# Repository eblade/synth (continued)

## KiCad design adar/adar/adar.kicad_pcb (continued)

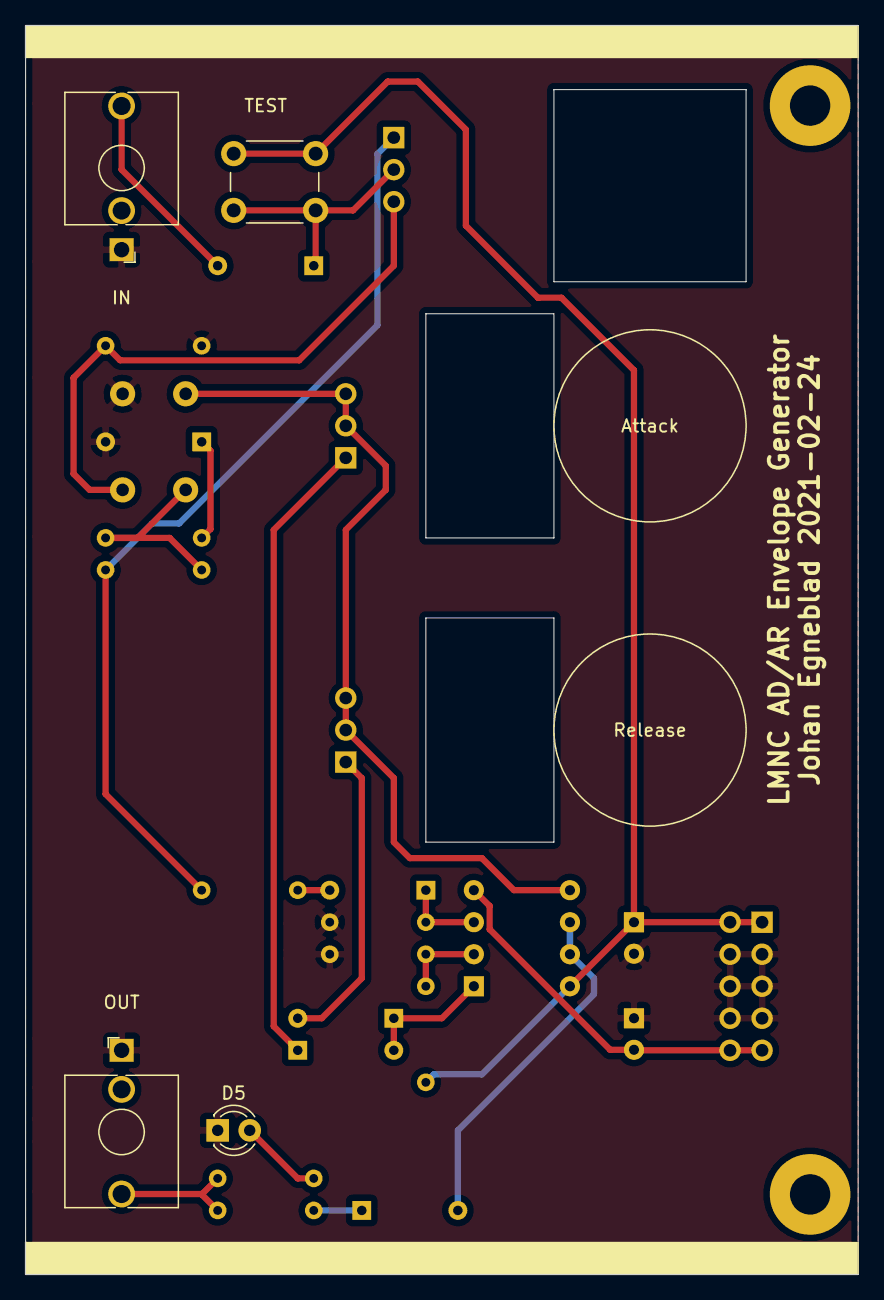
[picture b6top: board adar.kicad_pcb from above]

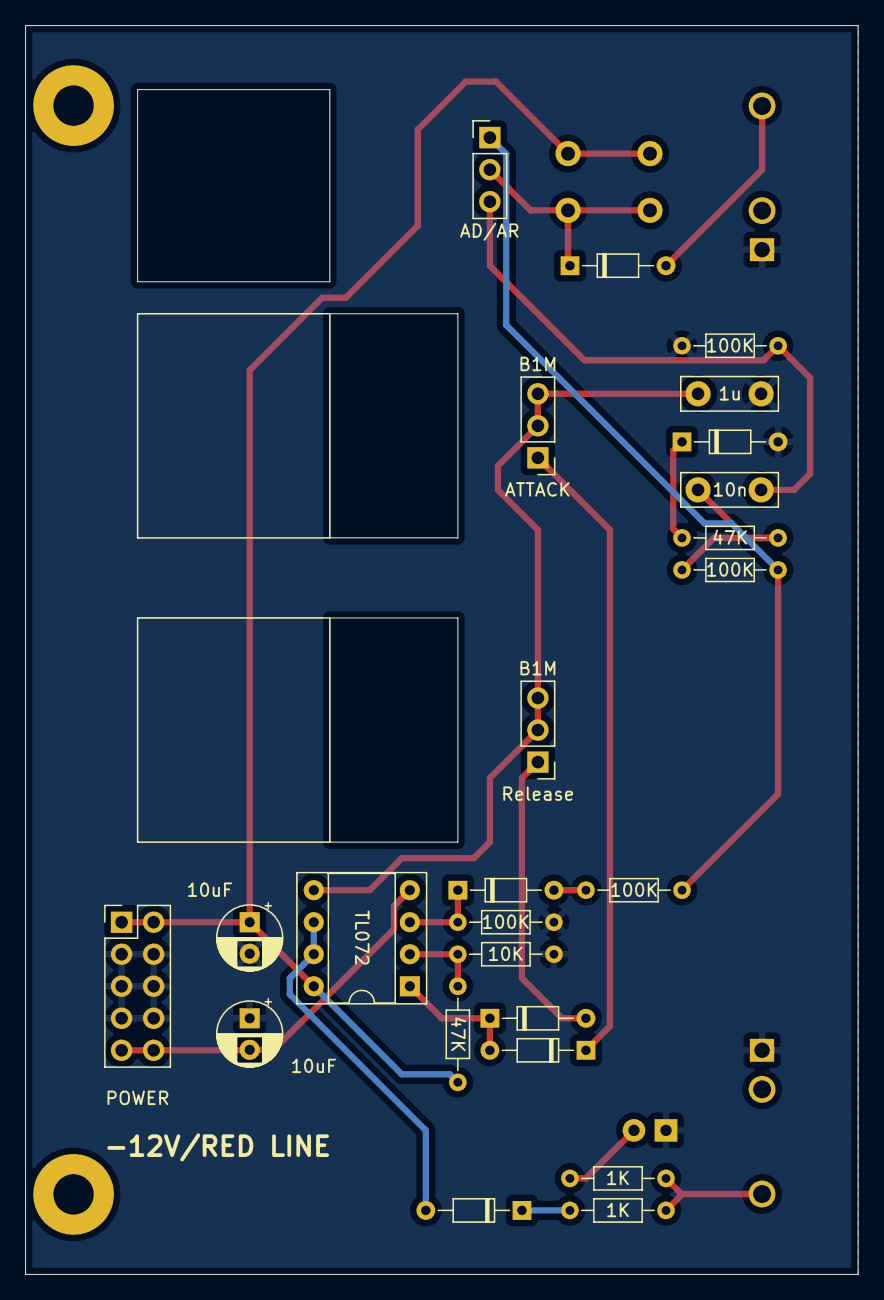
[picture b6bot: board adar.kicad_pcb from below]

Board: 2 copper layers, 66.0 x 99.1 mm, 30 parts (24 on the bottom side), 20 nets.

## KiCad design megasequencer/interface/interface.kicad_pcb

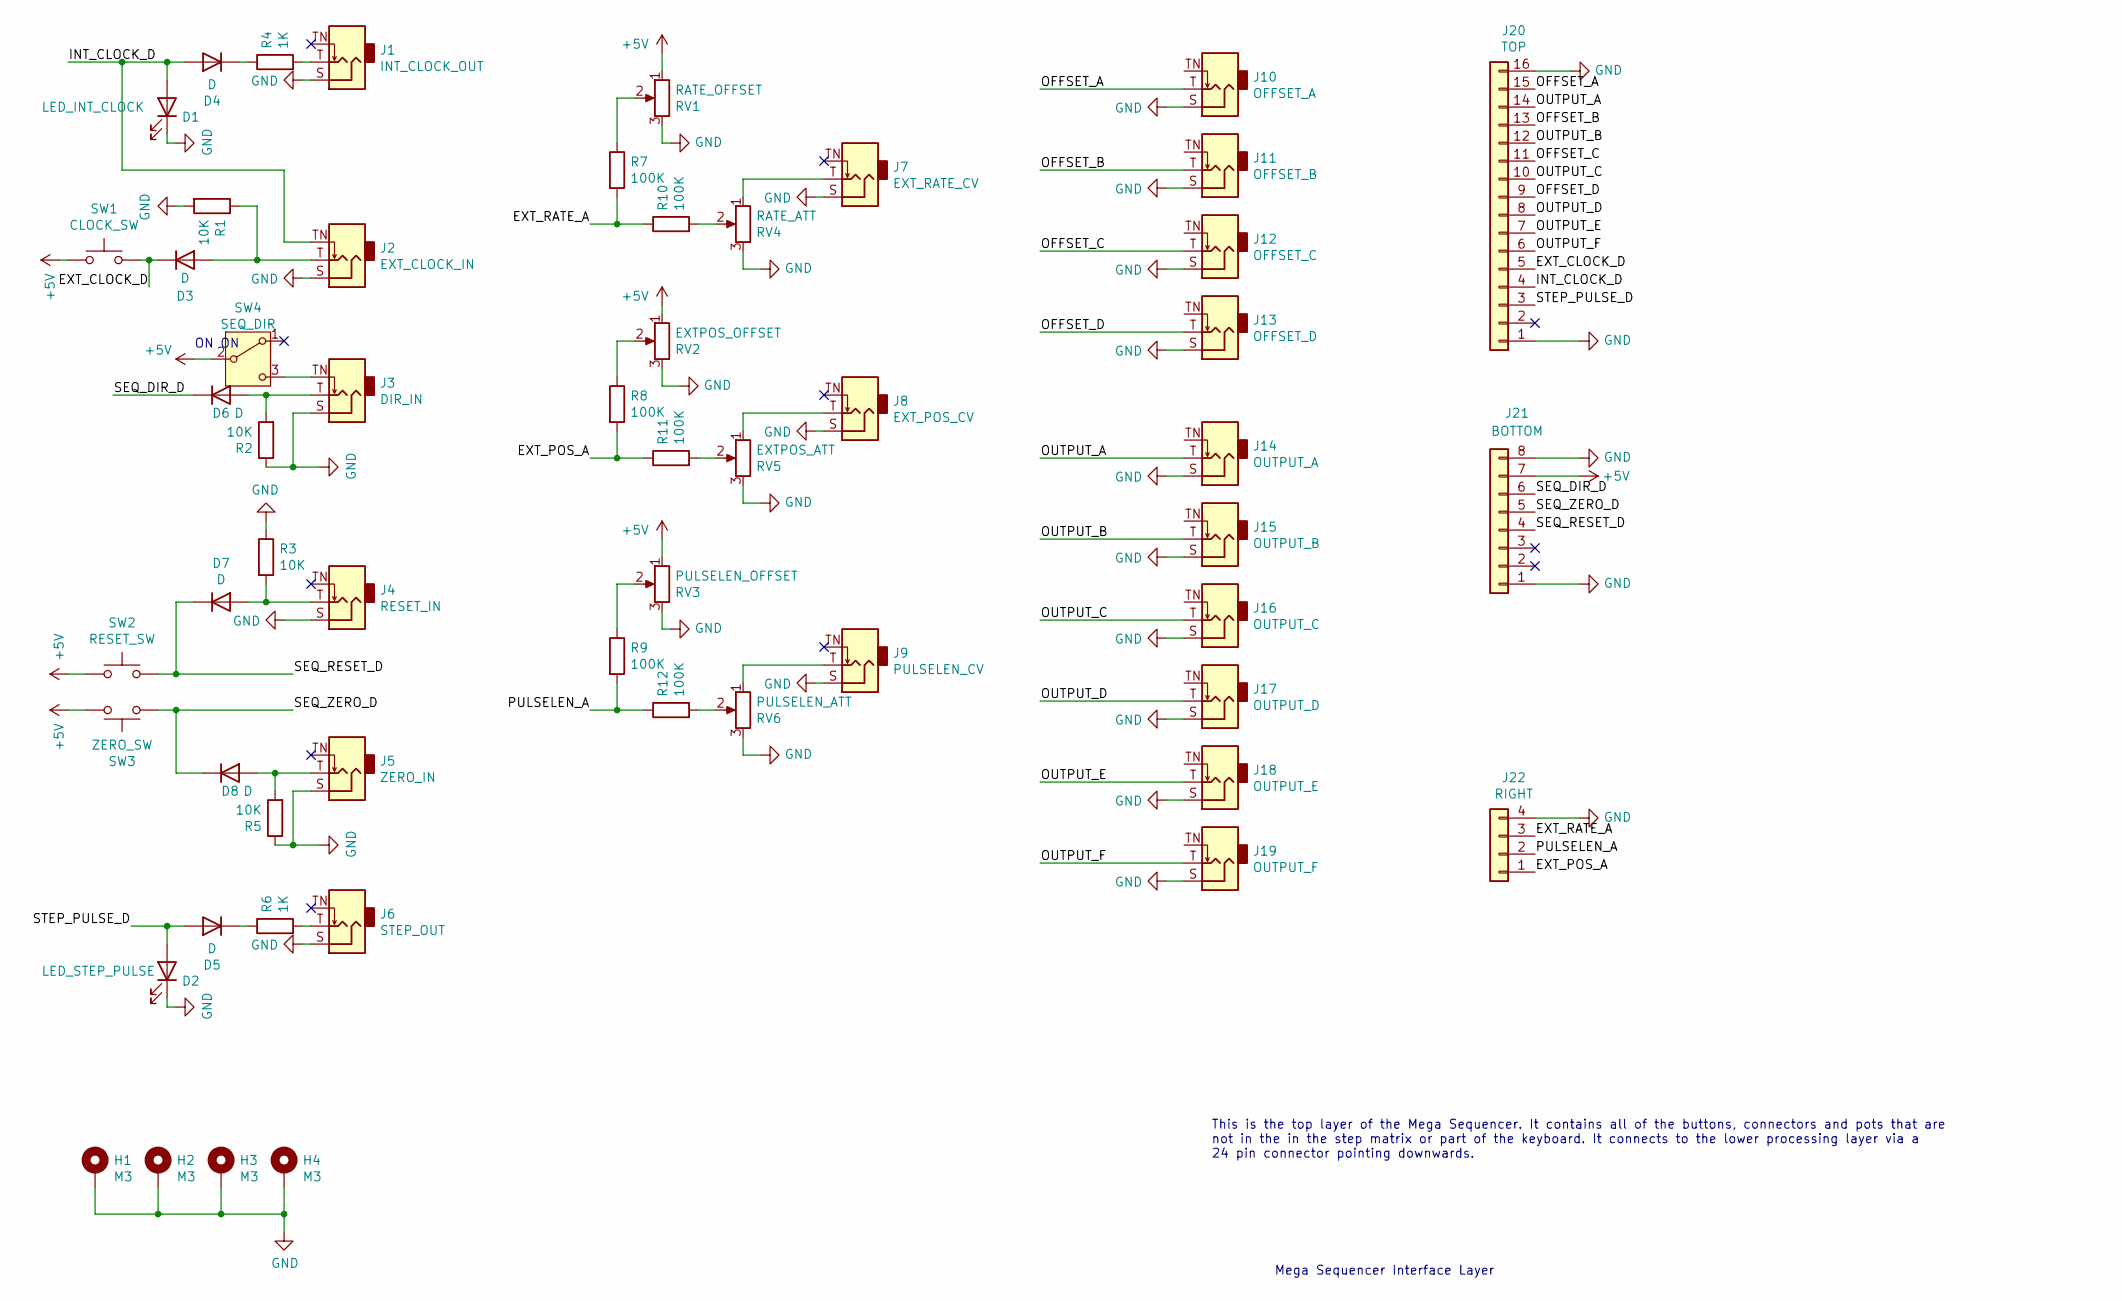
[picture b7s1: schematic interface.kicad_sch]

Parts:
D1: LED_INT_CLOCK; LED_D3.0mm
D2: LED_STEP_PULSE; LED_D3.0mm
D3, D4, D5, D6, D7, D8: D; D_DO-41_SOD81_P7.62mm_Horizontal
H1, H2, H3, H4: M3; MountingHole_3.2mm_M3_Pad
J1: INT_CLOCK_OUT; Jack_3.5mm_QingPu_WQP-PJ398SM_Vertical_CircularHoles
J2: EXT_CLOCK_IN; Jack_3.5mm_QingPu_WQP-PJ398SM_Vertical_CircularHoles
J3: DIR_IN; Jack_3.5mm_QingPu_WQP-PJ398SM_Vertical_CircularHoles
J4: RESET_IN; Jack_3.5mm_QingPu_WQP-PJ398SM_Vertical_CircularHoles
J5: ZERO_IN; Jack_3.5mm_QingPu_WQP-PJ398SM_Vertical_CircularHoles
J6: STEP_OUT; Jack_3.5mm_QingPu_WQP-PJ398SM_Vertical_CircularHoles
J7: EXT_RATE_CV; Jack_3.5mm_QingPu_WQP-PJ398SM_Vertical_CircularHoles
J8: EXT_POS_CV; Jack_3.5mm_QingPu_WQP-PJ398SM_Vertical_CircularHoles
J9: PULSELEN_CV; Jack_3.5mm_QingPu_WQP-PJ398SM_Vertical_CircularHoles
J10: OFFSET_A; Jack_3.5mm_QingPu_WQP-PJ398SM_Vertical_CircularHoles
J11: OFFSET_B; Jack_3.5mm_QingPu_WQP-PJ398SM_Vertical_CircularHoles
J12: OFFSET_C; Jack_3.5mm_QingPu_WQP-PJ398SM_Vertical_CircularHoles
J13: OFFSET_D; Jack_3.5mm_QingPu_WQP-PJ398SM_Vertical_CircularHoles
J14: OUTPUT_A; Jack_3.5mm_QingPu_WQP-PJ398SM_Vertical_CircularHoles
J15: OUTPUT_B; Jack_3.5mm_QingPu_WQP-PJ398SM_Vertical_CircularHoles
J16: OUTPUT_C; Jack_3.5mm_QingPu_WQP-PJ398SM_Vertical_CircularHoles
J17: OUTPUT_D; Jack_3.5mm_QingPu_WQP-PJ398SM_Vertical_CircularHoles
J18: OUTPUT_E; Jack_3.5mm_QingPu_WQP-PJ398SM_Vertical_CircularHoles
J19: OUTPUT_F; Jack_3.5mm_QingPu_WQP-PJ398SM_Vertical_CircularHoles
J20: TOP; PinHeader_1x16_P2.54mm_Vertical
J21: BOTTOM; PinHeader_1x08_P2.54mm_Vertical
J22: RIGHT; PinHeader_1x04_P2.54mm_Vertical
R1, R2, R3, R5: 10K; R_Axial_DIN0207_L6.3mm_D2.5mm_P7.62mm_Horizontal
R4, R6: 1K; R_Axial_DIN0207_L6.3mm_D2.5mm_P7.62mm_Horizontal
R7, R8, R9, R10, R11, R12: 100K; R_Axial_DIN0207_L6.3mm_D2.5mm_P7.62mm_Horizontal
RV1: RATE_OFFSET; Potentiometer_Alps_RK09L_Single_Vertical
RV2: EXTPOS_OFFSET; Potentiometer_Alps_RK09L_Single_Vertical
RV3: PULSELEN_OFFSET; Potentiometer_Alps_RK09L_Single_Vertical
RV4: RATE_ATT; Potentiometer_Alps_RK09L_Single_Vertical
RV5: EXTPOS_ATT; Potentiometer_Alps_RK09L_Single_Vertical
RV6: PULSELEN_ATT; Potentiometer_Alps_RK09L_Single_Vertical
SW1: CLOCK_SW; SW_PUSH_6mm
SW2: RESET_SW; SW_PUSH_6mm
SW3: ZERO_SW; SW_PUSH_6mm
SW4: SEQ_DIR; PinSocket_1x03_P2.54mm_Vertical

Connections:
+5V: J21.7, RV1.1, RV2.1, RV3.1, SW1.1, SW2.1, SW3.2, SW4.2 (B)
/EXT_CLOCK_D: D3.1 (K), J20.5, SW1.2
/EXT_POS_A: J22.1, R8.2, R11.1
/EXT_RATE_A: J22.3, R7.2, R10.1
/INT_CLOCK_D: D1.2 (A), D4.2 (A), J2.TN, J20.4
/OFFSET_A: J10.T, J20.15
/OFFSET_B: J11.T, J20.13
/OFFSET_C: J12.T, J20.11
/OFFSET_D: J13.T, J20.9
/OUTPUT_A: J14.T, J20.14
/OUTPUT_B: J15.T, J20.12
/OUTPUT_C: J16.T, J20.10
/OUTPUT_D: J17.T, J20.8
/OUTPUT_E: J18.T, J20.7
/OUTPUT_F: J19.T, J20.6
/PULSELEN_A: J22.2, R9.2, R12.1
/SEQ_DIR_D: D6.1 (K), J21.6
/SEQ_RESET_D: D7.1 (K), J21.4, SW2.2
/SEQ_ZERO_D: D8.1 (K), J21.5, SW3.1
/STEP_PULSE_D: D2.2 (A), D5.2 (A), J20.3
GND: D1.1 (K), D2.1 (K), H1.1, H2.1, H3.1, H4.1, J1.S, J2.S, J3.S, J4.S, J5.S, J6.S, J7.S, J8.S, J9.S, J10.S, J11.S, J12.S, J13.S, J14.S, J15.S, J16.S, J17.S, J18.S, J19.S, J20.1, J20.16, J21.1, J21.8, J22.4, R1.2, R2.1, R3.1, R5.1, RV1.3, RV2.3, RV3.3, RV4.3, RV5.3, RV6.3
unnamed: D3.2 (A), J2.T, R1.1
unnamed: D4.1 (K), R4.1
unnamed: D5.1 (K), R6.1
unnamed: D6.2 (A), J3.T, R2.2
unnamed: D7.2 (A), J4.T, R3.2
unnamed: D8.2 (A), J5.T, R5.2
unnamed: J1.T, R4.2
unnamed: J3.TN, SW4.3 (C)
unnamed: J6.T, R6.2
unnamed: J7.T, RV4.1
unnamed: J8.T, RV5.1
unnamed: J9.T, RV6.1
unnamed: R7.1, RV1.2
unnamed: R8.1, RV2.2
unnamed: R9.1, RV3.2
unnamed: R10.2, RV4.2
unnamed: R11.2, RV5.2
unnamed: R12.2, RV6.2

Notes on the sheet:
ON ON
Mega Sequencer Interface Layer
This is the top layer of the Mega Sequencer. It contains all of the buttons, connectors and pots that are not in the in the step matrix or part of the keyboard. It connects to the lower processing layer via a 24 pin connector pointing downwards.

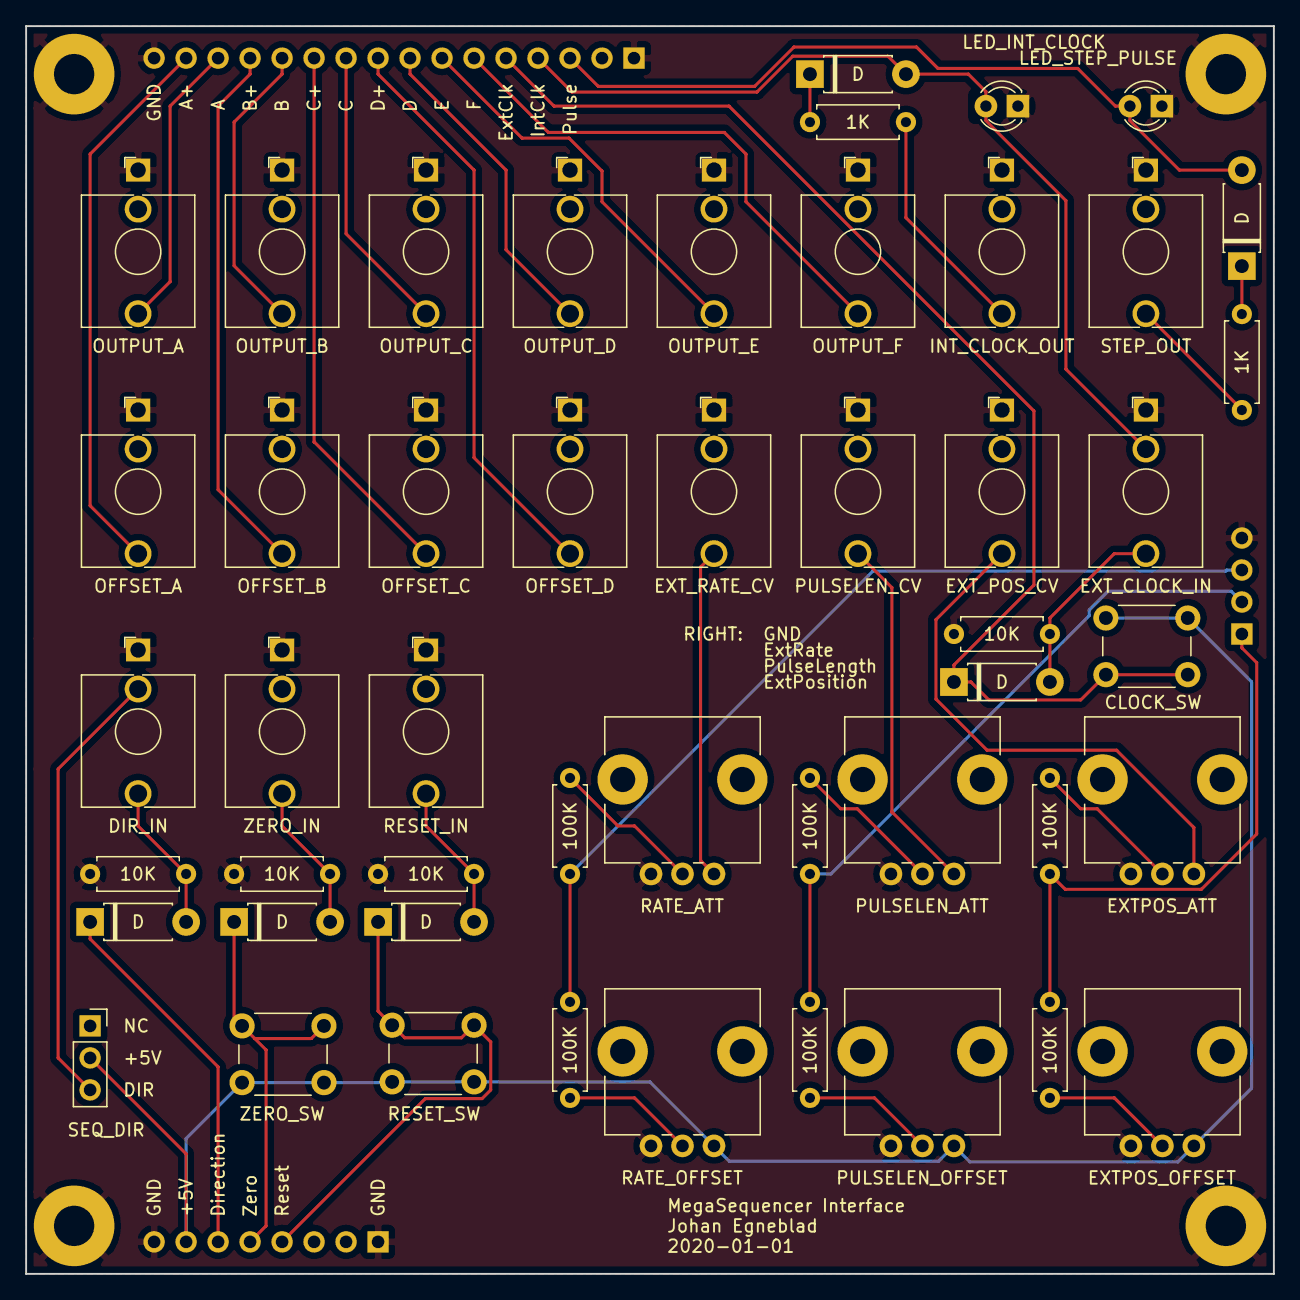
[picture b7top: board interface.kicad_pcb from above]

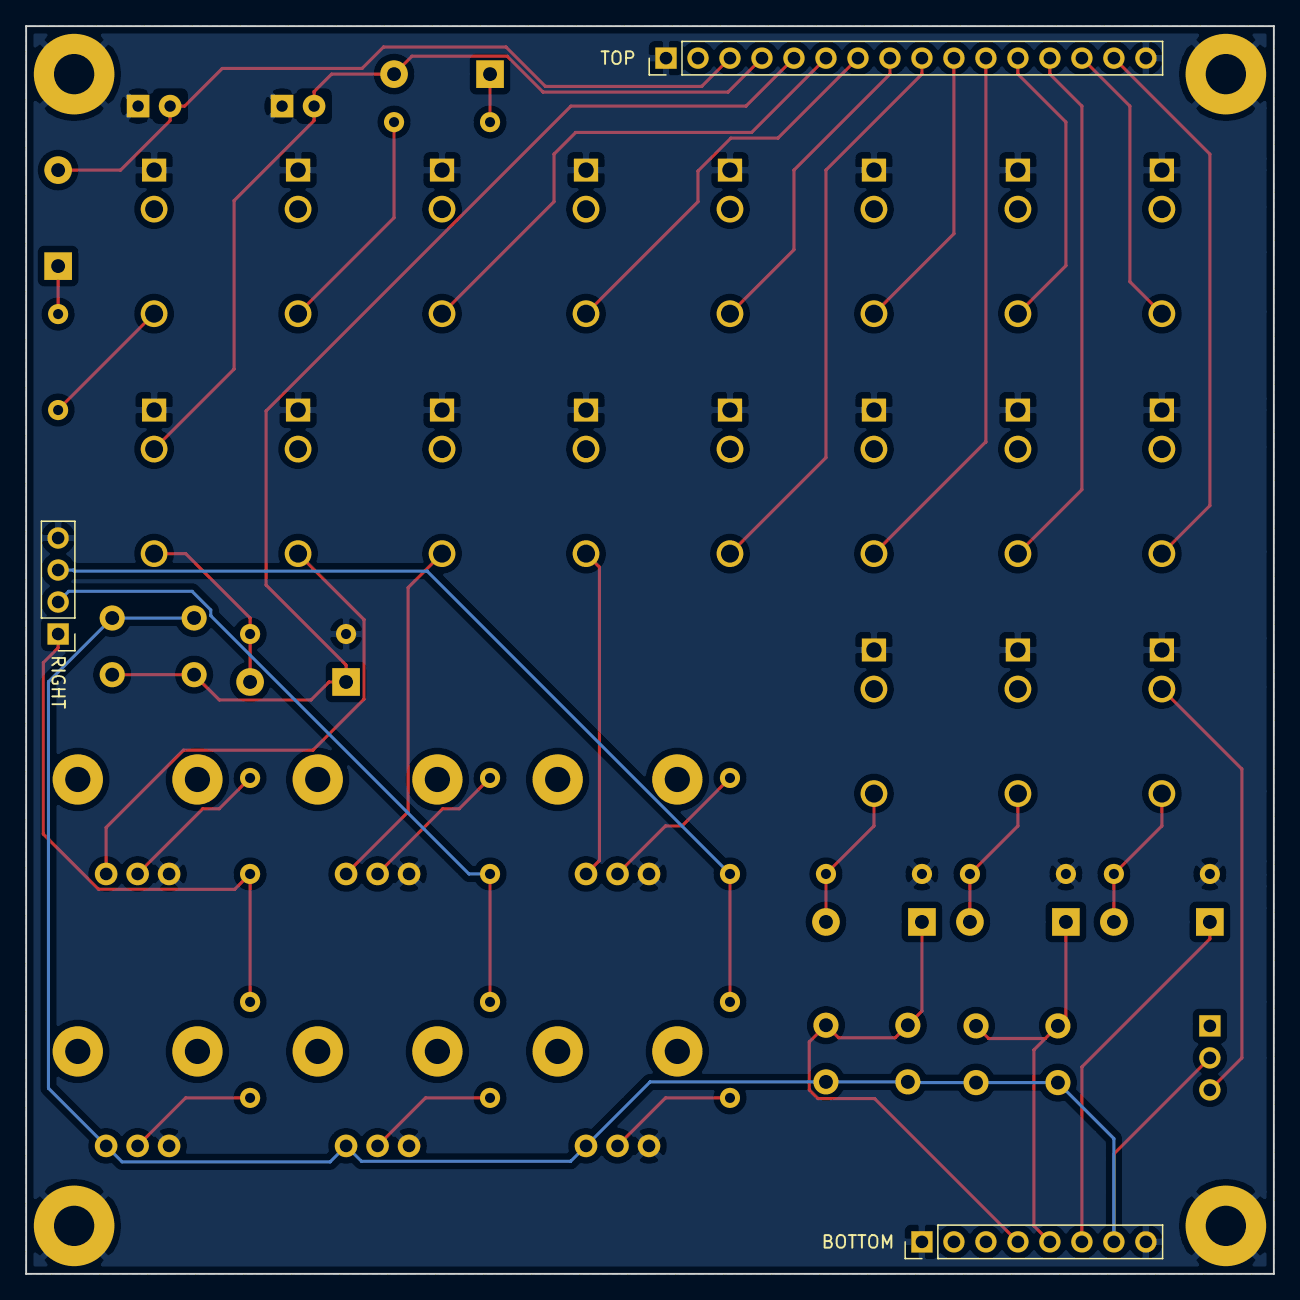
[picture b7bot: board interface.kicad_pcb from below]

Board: 2 copper layers, 99.1 x 99.1 mm, 56 parts (3 on the bottom side), 39 nets.

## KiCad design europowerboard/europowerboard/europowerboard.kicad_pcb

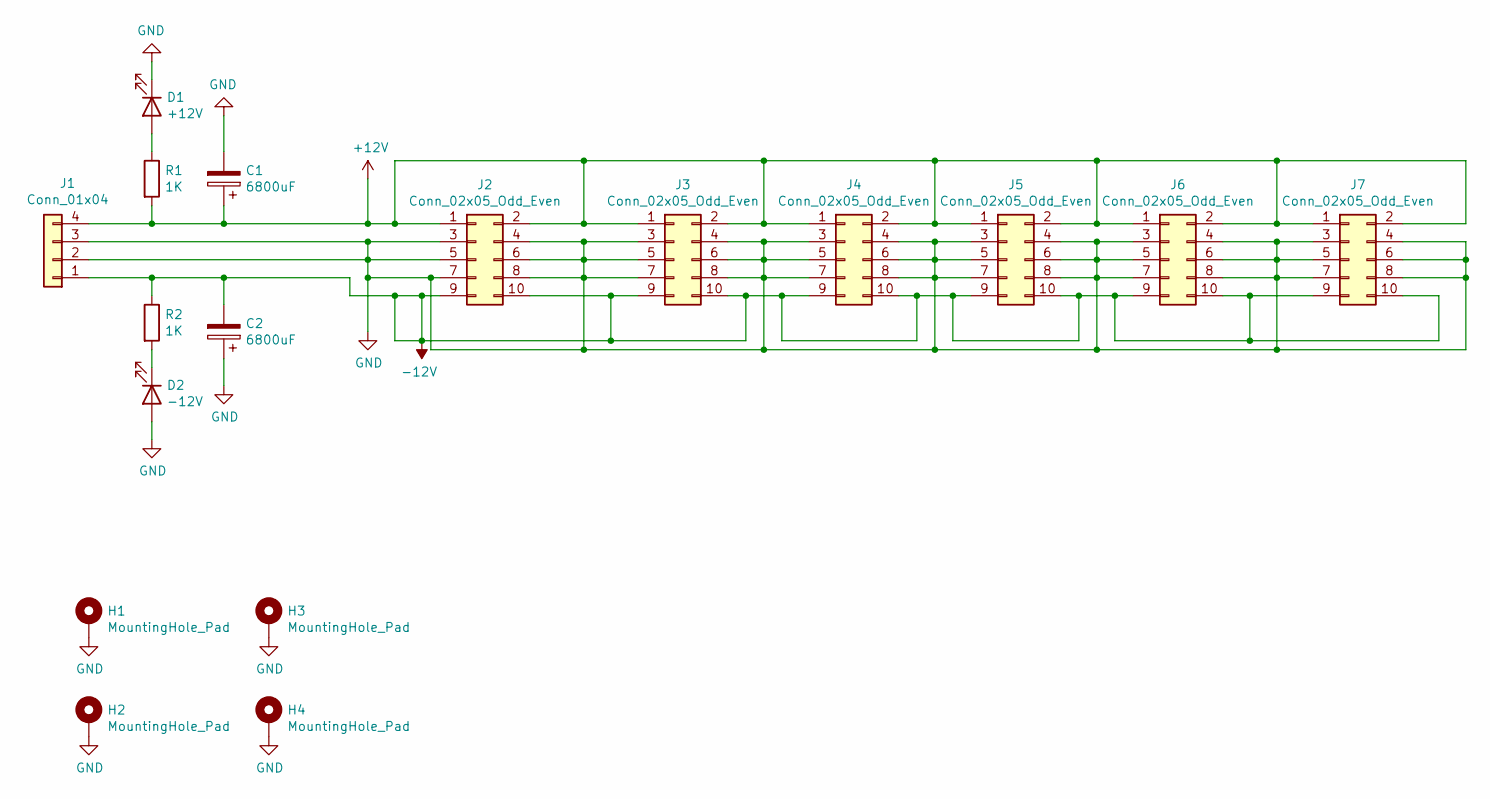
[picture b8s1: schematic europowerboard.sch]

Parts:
C1, C2: 6800uF; CP_Radial_D25.0mm_P10.00mm_SnapIn
D1: +12V; LED_D5.0mm
D2: -12V; LED_D5.0mm
H1, H2, H3, H4: MountingHole_Pad; MountingHole_3.2mm_M3_Pad
J1: Conn_01x04; PhoenixContact_MSTBA_2,5_4-G-5,08_1x04_P5.08mm_Horizontal
J2, J3, J4, J5, J6, J7: Conn_02x05_Odd_Even; PinHeader_2x05_P2.54mm_Vertical
R1, R2: 1K; R_Axial_DIN0207_L6.3mm_D2.5mm_P10.16mm_Horizontal

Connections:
+12V: C1.1, J1.4, J2.1, J2.2, J3.1, J3.2, J4.1, J4.2, J5.1, J5.2, J6.1, J6.2, J7.1, J7.2, R1.2
-12V: C2.2, J1.1, J2.9, J2.10, J3.9, J3.10, J4.9, J4.10, J5.9, J5.10, J6.9, J6.10, J7.9, J7.10, R2.1
GND: C1.2, C2.1, D1.1 (K), D2.2 (A), H1.1, H2.1, H3.1, H4.1, J1.2, J1.3, J2.3, J2.4, J2.5, J2.6, J2.7, J2.8, J3.3, J3.4, J3.5, J3.6, J3.7, J3.8, J4.3, J4.4, J4.5, J4.6, J4.7, J4.8, J5.3, J5.4, J5.5, J5.6, J5.7, J5.8, J6.3, J6.4, J6.5, J6.6, J6.7, J6.8, J7.3, J7.4, J7.5, J7.6, J7.7, J7.8
unnamed: D1.2 (A), R1.1
unnamed: D2.1 (K), R2.2

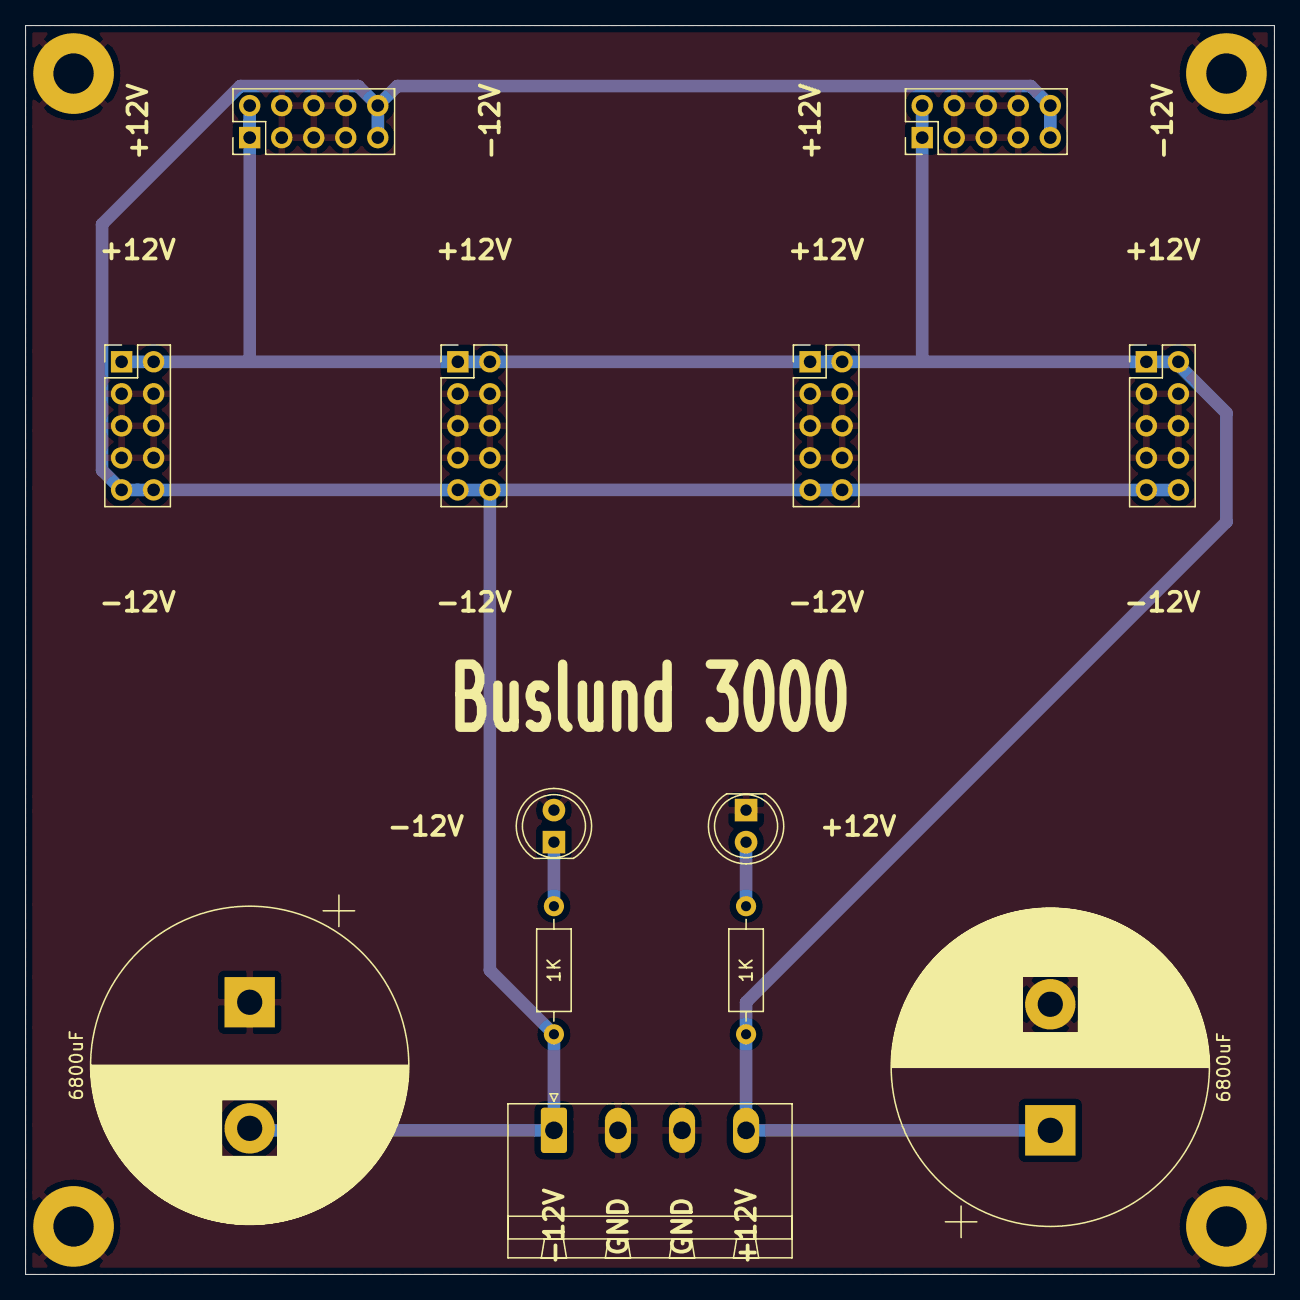
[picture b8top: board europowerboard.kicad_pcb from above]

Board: 2 copper layers, 99.1 x 99.1 mm, 17 parts (0 on the bottom side), 5 nets.

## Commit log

2019-11-10 Fixed offsetscaler and added some megasequencer ideas and resources
2019-11-11 Start working with brain of the mega sequencer
2019-11-11 More info
2019-11-11 Formatting
2019-11-11 Remove a switch and declutter the doc somewhat
2019-11-12 Some docs after inventory
2019-11-12 MD links
2019-11-13 Add the rhythm sequencer stripboard layout
2019-11-21 Add more jacks to the schema
2019-11-21 Got to make this into a module
2019-11-23 Add int clock out
2019-11-23 Split up into sub schemas and add layout sketch
2019-11-25 Add pwr, more inputs and outputs
2019-11-27 Fiddling with PCB a bit
2019-12-21 Fix some bugs and connect the digital IOs and setps out
2019-12-25 Split brain into brain and interface pcbs, so everything fits
2019-12-26 Finish interface and continue with brain
2019-12-27 Brain seem ok now, also start charting the program
2019-12-28 Almost done now with both pcbs
2020-01-01 Finish up labeling and fixa connector that was in the wrong direction
2020-01-02 Add some info on capacitive touch sensors
2020-01-02 Another link
2020-01-04 Labeling
2020-01-04 Start with VCO from LMNC
2020-01-06 Add europower module that filters power and finish vco schamatics
2020-01-07 Increase trace width on brain, start sorting stuff for vco and start writing shopping list
2020-01-11 Extra 7805 footprint, new standard, and some order to the VCO chaos
2020-01-11 More shopping
2020-01-18 Settled at larger pcb, think its going to work with components placed like this
2020-01-18 All wired up, slightly different layout
2020-01-19 Started with the panel
2020-01-26 Add more text to panel
2020-01-26 Make the offset scaler fit the new standard
2020-01-26 Move some text
2020-02-05 Place some holes
2020-02-12 All holes done
2020-05-05 Sent off lots off stuff for etsing
2020-05-27 Add faust folder and some small changes
2020-06-09 Add panel drill guide
2020-06-17 Add print panel graphics
2020-09-22 Add a noise patch
2020-09-25 First shot on writing that code
2020-09-29 Good to have I guess
2020-09-29 Buslund 3000
2020-10-31 Add layout files
2020-11-24 Wrong LED direction
2021-03-07 Add adar plus some megasequencer updates
2021-04-07 Start work on Quad VCA with Mixer module
2021-04-17 Add VCA wip (no lines yet)
2021-04-17 Add some docs for SSI2164 Quad VCA
2021-04-18 Route the VCA
2021-05-01 Add VCA panel plus noise module
2021-09-18 Made schematic for VCLFO
2021-09-20 PDFs that are nice
2021-09-22 Fix bugs and add footprints
2021-09-30 Start fiddling with the PCB for the VCLFO
2021-10-05 Place all the stuffs
2021-10-05 Route the VCLFO
2021-12-01 Working with that VCF
2021-12-14 Time to route
2021-12-16 The VCF is routed. Finally
2022-01-11 Made the VCF panel
2022-01-13 Add LFO panel
2022-01-17 Gerber files done, ordered the stuff
2022-03-22 KiCad 6.0 upgrade
2023-01-05 LFO and VCF (the latter does not seem to work though)
2024-05-06 Add 8bit dvco and update some project files
2024-09-09 done without errors and warnings
2024-09-18 Finish that 8bit synth board and send it off
